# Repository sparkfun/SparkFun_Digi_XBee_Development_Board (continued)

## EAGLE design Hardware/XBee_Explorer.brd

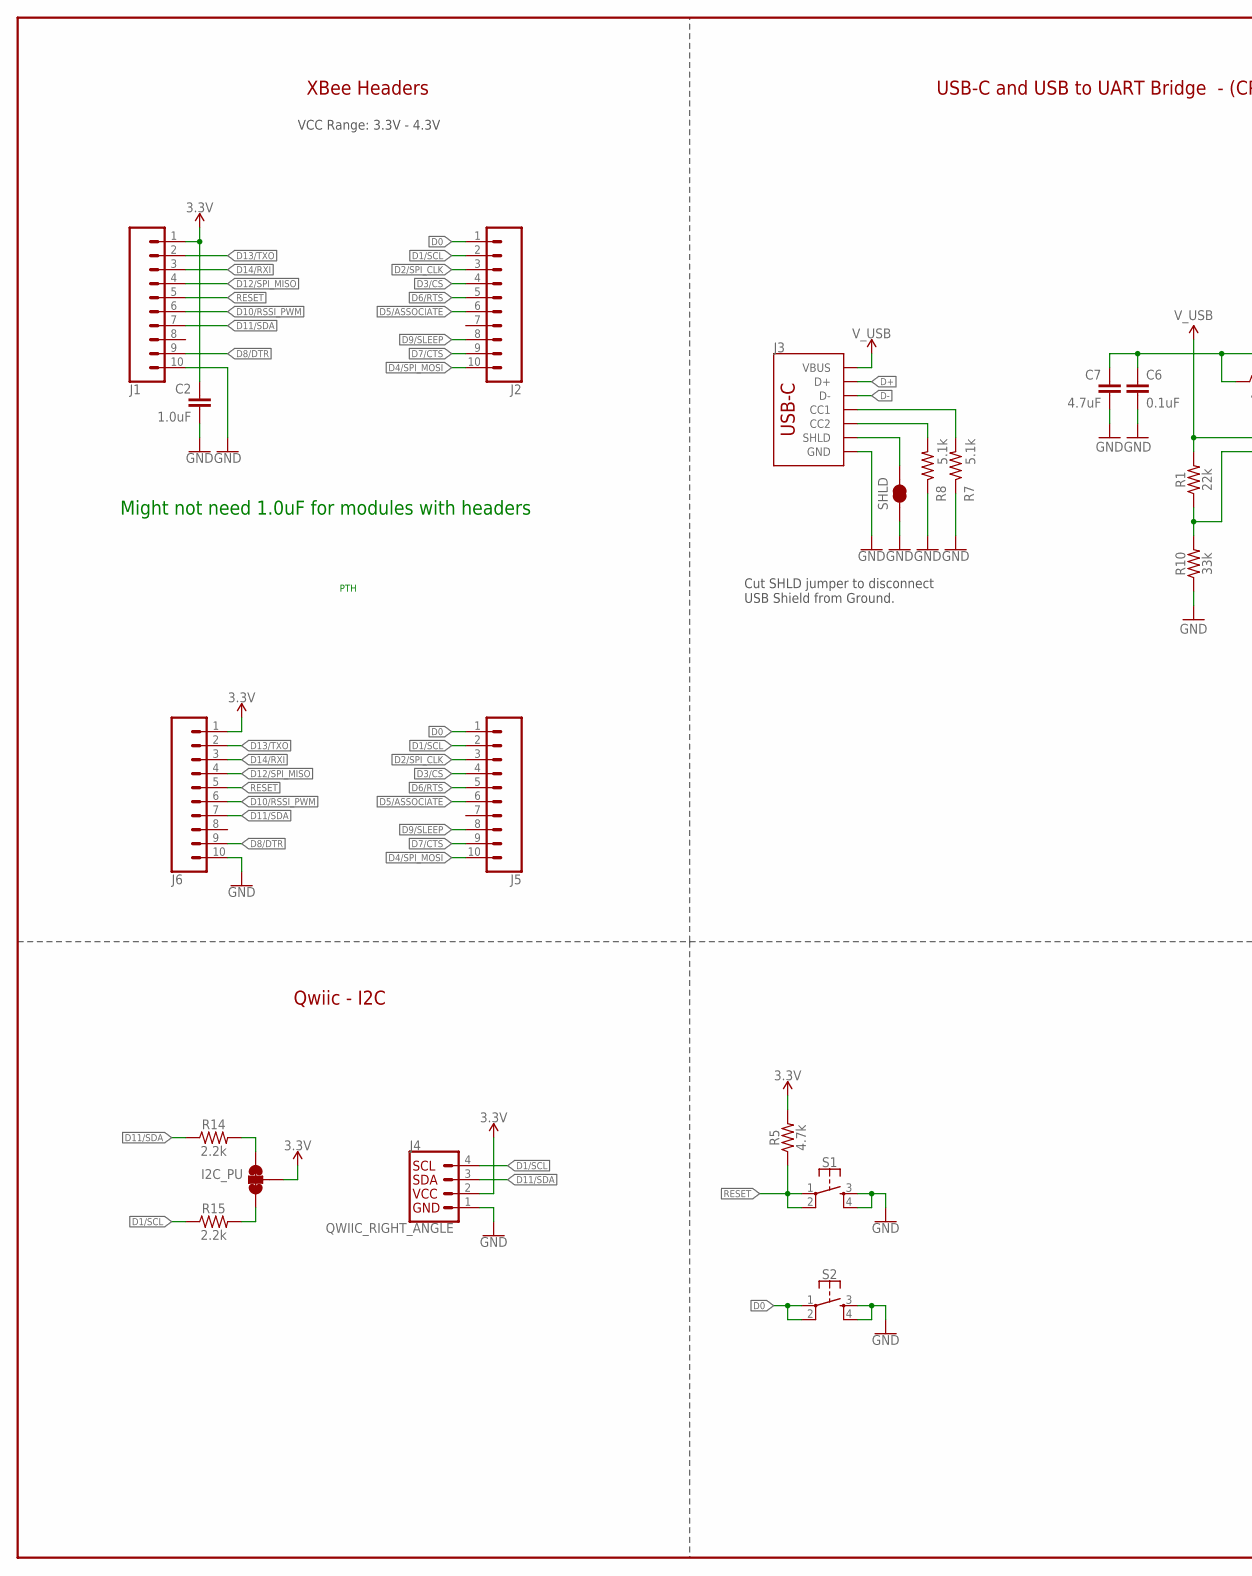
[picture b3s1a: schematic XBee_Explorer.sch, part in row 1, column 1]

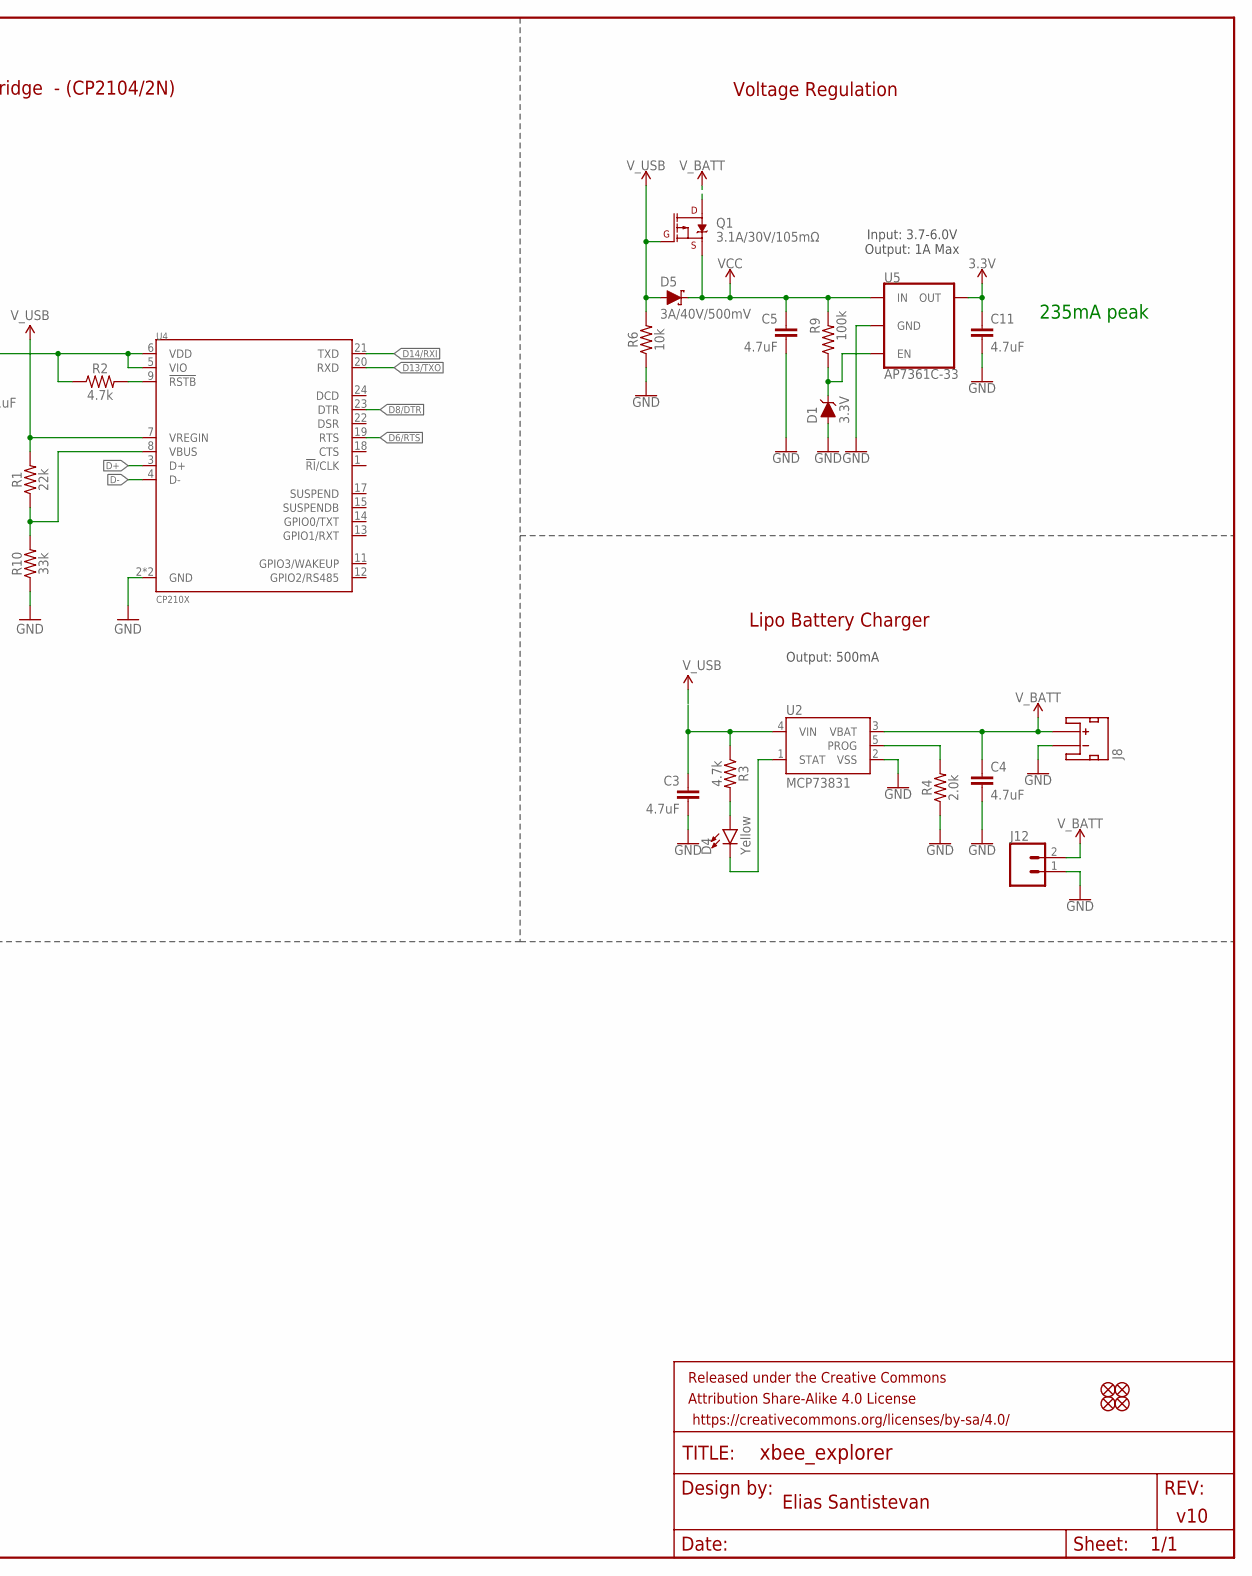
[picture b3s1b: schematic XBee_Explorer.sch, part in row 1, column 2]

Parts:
C2: 1.0uF; 0603
C3, C4, C5, C7, C11: 4.7uF; 0603
C6: 0.1uF; 0603
D1: 3.3V; SOD-323
D4: Yellow; LED-0603
D5: 3A/40V/500mV; SMA-DIODE
FD1, FD2, FD3, FD4: FIDUCIAL1X2; FIDUCIAL-1X2
FRAME1: FRAME-LEDGER; CREATIVE_COMMONS
I2C_PU: JUMPER-SMT_3_2-NC_TRACE_SILK; SMT-JUMPER_3_2-NC_TRACE_SILK
J1, J2, J5, J6: CONN_10NO_SILK_PTH_FEMALE; 1X10_NO_SILK
J3: USB_C_2-LAYER_PADS; USB-C-16P-2LAYER-PADS
J4: QWIIC_RIGHT_ANGLE; JST04_1MM_RA
J8: JST_2MM_MALE; JST-2-SMD
J12: CONN_021X02_NO_SILK; 1X02_NO_SILK
Q1: 3.1A/30V/105mΩ; SOT23-3
R1: 22k; 0603
R2, R3, R5: 4.7k; 0603
R4: 2.0k; 0603
R6: 10k; 0603
R7, R8: 5.1k; 0603
R9: 100k; 0603
R10: 33k; 0603
R14, R15: 2.2k; 0603
S1, S2: MOMENTARY-SWITCH-SPST-2-SMD-5.2MM-TALL; TACTILE_SWITCH_SMD_5.2MM
SHLD: JUMPER-SMT_2_NC_TRACE_SILK; SMT-JUMPER_2_NC_TRACE_SILK
U2: MCP73831; SOT23-5
U4: CP210X; QFN24
U5: AP7361C-33; UDFN-8

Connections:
3.3V: C2.1, C11.1, I2C_PU.2, J1.1, J4.2, J6.1, R5.2, U5.1 (OUT)
3.3V_EN_VE: D1.C, R9.1, U5.5 (EN)
!RESET!: J1.5, J6.5, R5.1, S1.1, S1.2
D0: J2.1, J5.1, S2.1, S2.2
D1/SCL: J2.2, J4.4, J5.2, R15.1
D2/SPI_CLK: J2.3, J5.3
D3/!CS!: J2.4, J5.4
D4/SPI_MOSI: J2.10, J5.10
D5/ASSOCIATE: J2.6, J5.6
D6/!RTS!: J2.5, J5.5, U4.19 (RTS)
D7/!CTS!: J2.9, J5.9
D8/!DTR!: J1.9, J6.9, U4.23 (DTR)
D9/!SLEEP!: J2.8, J5.8
D10/RSSI_PWM: J1.6, J6.6
D11/SDA: J1.7, J4.3, J6.7, R14.1
D12/SPI_MISO: J1.4, J6.4
D13/TXO: J1.2, J6.2, U4.20 (RXD)
D14/RXI: J1.3, J6.3, U4.21 (TXD)
D+: J3.A6 (D+), J3.B6 (D+), U4.3 (D+)
D-: J3.A7 (D-), J3.B7 (D-), U4.4 (D-)
GND: C2.2, C3.2, C4.2, C5.2, C6.2, C7.2, C11.2, D1.A, J1.10, J3.GND, J3.GND2 (GND), J4.1, J6.10, J8.1 (-), J12.1, R4.1, R6.1, R7.1, R8.1, R10.1, S1.3, S1.4, S2.3, S2.4, SHLD.1, U2.2 (VSS), U4.2 (GND), U4.PAD (GND), U5.4 (GND), U5.EP (GND)
unnamed: R4.2, U2.5 (PROG)
unnamed: R1.1, R10.2, U4.8 (VBUS)
unnamed: C6.1, C7.1, R2.1, U4.5 (VIO), U4.6 (VDD)
unnamed: J3.B5 (CC2), R8.2
unnamed: J3.A5 (CC1), R7.2
unnamed: R2.2, U4.9 (!RSTB)
unnamed: D4.C, U2.1 (STAT)
unnamed: D4.A, R3.2
unnamed: C3.1, R3.1, U2.4 (VIN)
unnamed: I2C_PU.3, R14.2
unnamed: I2C_PU.1, R15.2
SHLD: J3.SHLD1 (SHLD), J3.SHLD2 (SHLD), J3.SHLD3 (SHLD), J3.SHLD4 (SHLD), SHLD.2
VCC: C5.1, D5.C, Q1.2 (S), R9.2, U5.8 (IN)
V_BATT: C4.1, J8.2 (+), J12.2, Q1.3 (D), U2.3 (VBAT)
V_USB: D5.A, J3.VBUS1 (VBUS), J3.VBUS2 (VBUS), Q1.1 (G), R1.2, R6.2, U4.7 (VREGIN)

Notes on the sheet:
VCC Range: 3.3V - 4.3V
USB-C and USB to UART Bridge - (CP2104/2N)
Voltage Regulation
Input: 3.7-6.0V Output: 1A Max
Lipo Battery Charger
Output: 500mA
Cut SHLD jumper to disconnect USB Shield from Ground.
XBee Headers
Qwiic - I2C
235mA peak
v10
Elias Santistevan
Might not need 1.0uF for modules with headers
PTH

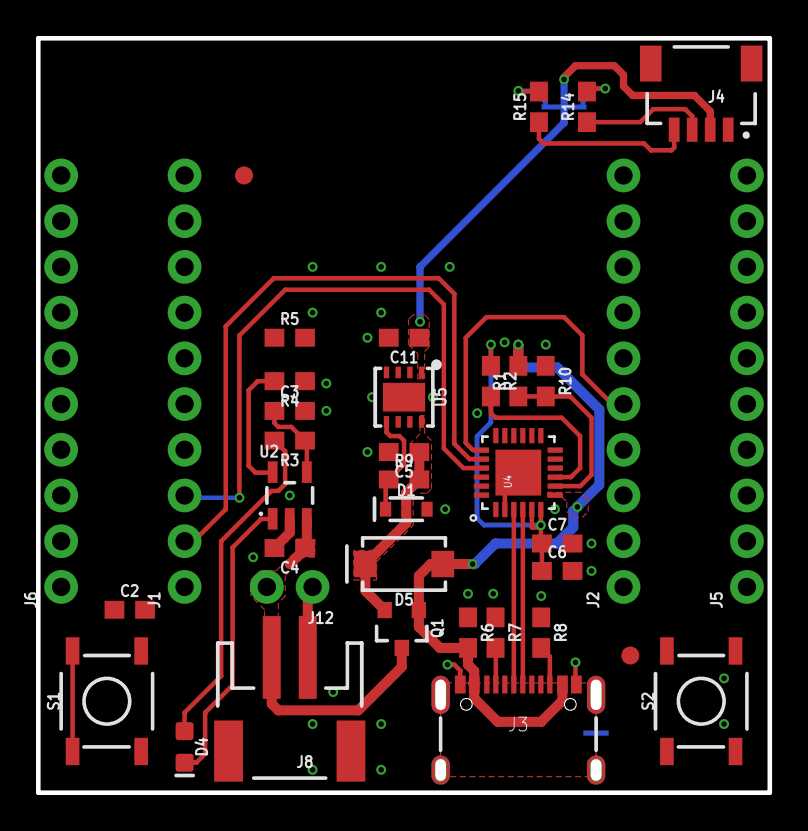
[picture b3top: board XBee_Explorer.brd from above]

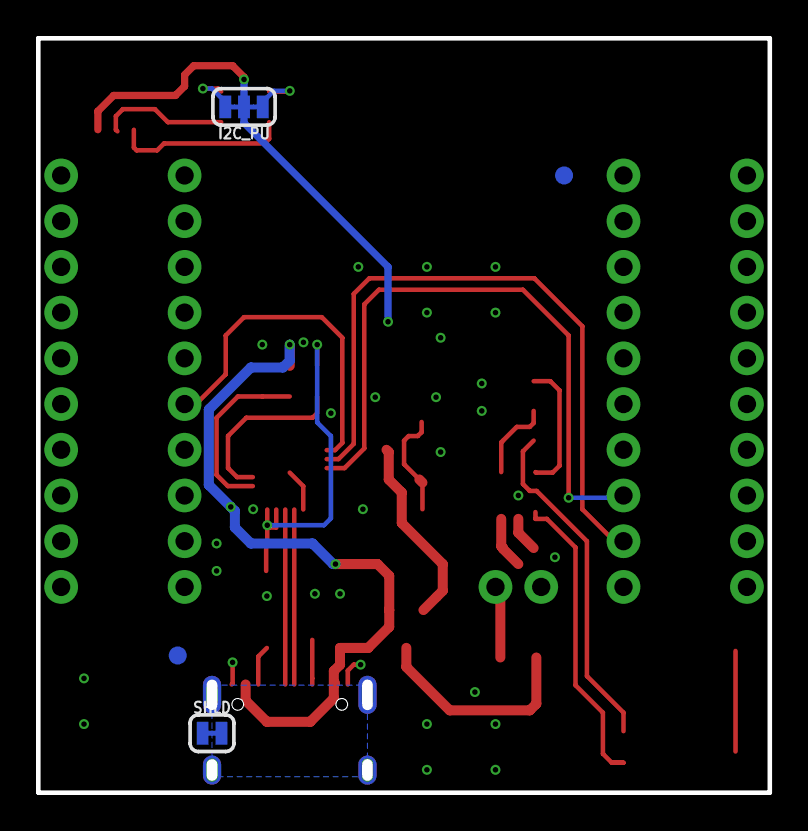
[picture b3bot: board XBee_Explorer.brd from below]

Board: 2 copper layers, 40.6 x 41.9 mm, 43 parts (4 on the bottom side), 36 nets.

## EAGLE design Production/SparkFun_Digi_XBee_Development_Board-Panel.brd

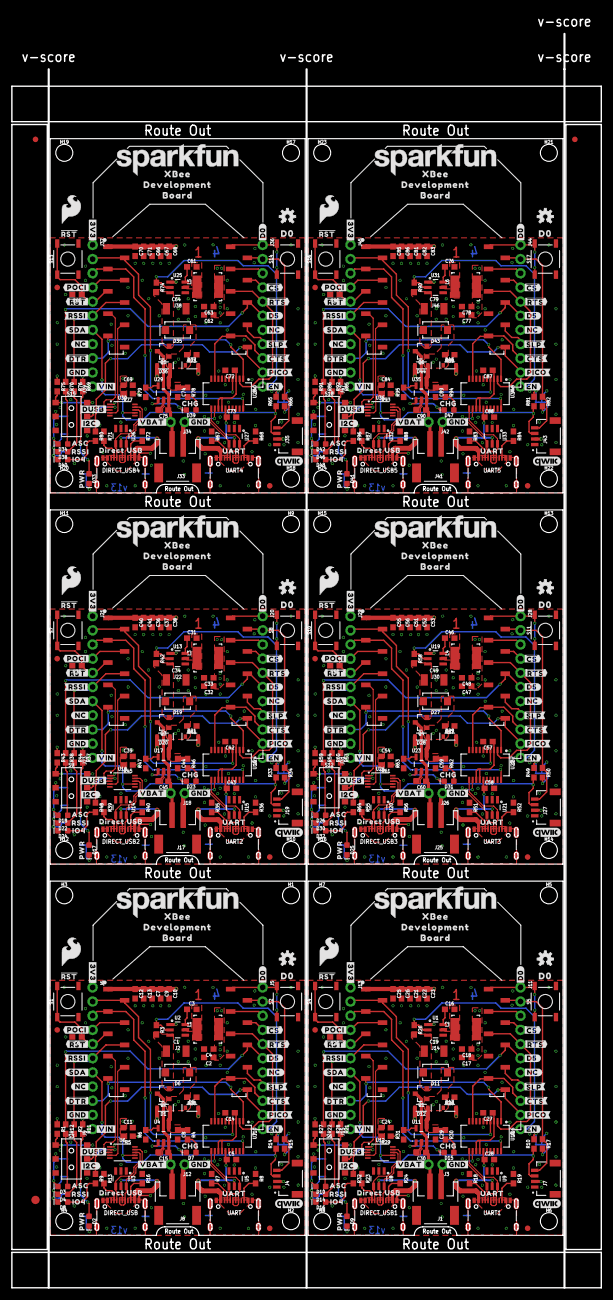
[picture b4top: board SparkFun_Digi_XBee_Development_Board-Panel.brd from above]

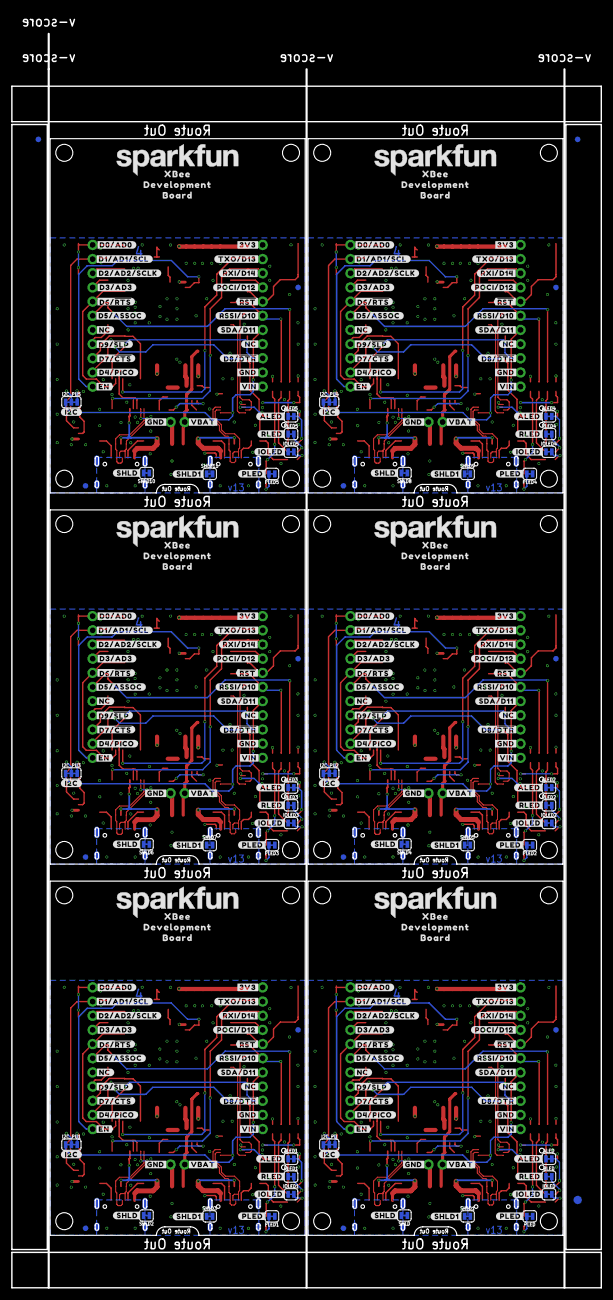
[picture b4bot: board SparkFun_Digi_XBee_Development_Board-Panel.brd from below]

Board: 4 copper layers, 105.7 x 224.8 mm, 894 parts (267 on the bottom side), 330 nets.

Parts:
ALED, ALED1, ALED2, ALED3, ALED4, ALED5: JUMPER-SMT_2_NC_TRACE_SILK; SMT-JUMPER_2_NC_TRACE_SILK
C1, C19, C34, C49, C64, C79: 10uF; 1210
C2, C4, C17, C18, C32, C33, C47, C48, C62, C63, C77, C78: 22uF; 0603
C3, C5, C9, C11, C14, C16, C22, C24, C27, C28, C31, C37, C39, C42, C43, C46, C52, C54, C57, C58, C61, C67, C69, C72, C73, C76, C82, C84, C87, C88: 0.1uF; 0603
C6, C7, C20, C21, C35, C36, C50, C51, C65, C66, C80, C81: 10nF; 0603
C8, C15, C29, C30, C44, C45, C59, C60, C74, C75, C89, C90: 4.7uF; 0603
C10, C23, C38, C53, C68, C83: 10uF; 0603
C12, C25, C40, C55, C70, C85: 10pF; 0603
C13, C26, C41, C56, C71, C86: 47pF; 0603
D1, D5, D12, D13, D20, D21, D28, D29, D36, D37, D44, D45: 3A/10V/280mV; SOD-323
D2, D9, D17, D25, D33, D41: RED; LED-0603
D3, D10, D18, D26, D34, D42: BLUE; LED-0603
D4, D7, D14, D15, D22, D23, D30, D31, D38, D39, D46, D47: Yellow; LED-0603
D6, D11, D19, D27, D35, D43: 3A/40V/500mV; SMA-DIODE
D8, D16, D24, D32, D40, D48: GREEN; LED-0603
DIRECT_USB, DIRECT_USB1, DIRECT_USB2, DIRECT_USB3, DIRECT_USB4, DIRECT_USB5: USB Female Type C Connector; USB-C-16P-4LAYER-ISOLATED
E$1, E$2, E$3, E$4: FIDUCIAL-1X2
E$5, E$6: FIDUCIAL-1.5X3
FD1, FD2, FD3, FD4, FD5, FD6, FD7, FD8, FD9, FD10, FD11, FD12, FD13, FD14, FD15, FD16, FD17, FD18, FD19, FD20, FD21, FD22, FD23, FD24: FIDUCIAL1X2; FIDUCIAL-1X2
H1, H2, H3, H4, H5, H6, H7, H8, H9, H10, H11, H12, H13, H14, H15, H16, H17, H18, H19, H20, H21, H22, H23, H24: STAND-OFFTIGHT; STAND-OFF-TIGHT
I2C_PU, I2C_PU1, I2C_PU2, I2C_PU3, I2C_PU4, I2C_PU5: JUMPER-SMT_3_2-NC_TRACE_SILK; SMT-JUMPER_3_2-NC_TRACE_SILK
IOLED, IOLED1, IOLED2, IOLED3, IOLED4, IOLED5: JUMPER-SMT_2_NC_TRACE_SILK; SMT-JUMPER_2_NC_TRACE_SILK
J1, J8, J17, J25, J33, J41: JST-2-SMD
J2, J14, J22, J30, J38, J46: XBEE3-SMD
J3, J12, J18, J26, J34, J42: 1X02_NO_SILK
J4, J7, J19, J27, J35, J43: QWIIC_RIGHT_ANGLE; JST04_1MM_RA
J5, J6, J11, J13, J20, J21, J28, J29, J36, J37, J44, J45: 1X10_NO_SILK
J9, J10, J15, J16, J23, J24, J31, J32, J39, J40, J47, J48: 1X01_NO_SILK_STAND
L1, L2, L3, L4, L5, L6: 3.9UH; INDUCTOR_3.9UH
LOGO1, LOGO6, LOGO9, LOGO12, LOGO15, LOGO18: SFE_LOGO_NAME.2_INCH; SFE_LOGO_NAME_.2
LOGO2, LOGO4, LOGO7, LOGO10, LOGO13, LOGO16: OSHW-LOGOS; OSHW-LOGO-S
LOGO3, LOGO5, LOGO8, LOGO11, LOGO14, LOGO17: QWIIC_LOGO_5MM; QWIIC_5MM
PLED, PLED1, PLED2, PLED3, PLED4, PLED5: JUMPER-SMT_2_NC_TRACE_SILK; SMT-JUMPER_2_NC_TRACE_SILK
Q1, Q2, Q3, Q4, Q5, Q6: 3.1A/30V/105mΩ; SOT23-3
R1, R27, R43, R59, R75, R91: 100k; 0603
R2, R10, R12, R14, R15, R17, R22, R28, R33, R34, R38, R44, R49, R50, R54, R60, R65, R66, R70, R76, R81, R82, R86, R92: 2.2k; 0603
R3, R20, R25, R26, R41, R42, R57, R58, R73, R74, R89, R90: 10k; 0603
R4, R11, R21, R30, R37, R46, R53, R62, R69, R78, R85, R94: 4.7k; 0603
R5, R29, R45, R61, R77, R93: 0; 0603
R6, R31, R47, R63, R79, R95: 2.0k; 0603
R7, R8, R13, R16, R18, R19, R23, R24, R35, R36, R39, R40, R51, R52, R55, R56, R67, R68, R71, R72, R83, R84, R87, R88: 5.1k; 0603
R9, R32, R48, R64, R80, R96: 330; 0603
RLED, RLED1, RLED2, RLED3, RLED4, RLED5: JUMPER-SMT_2_NC_TRACE_SILK; SMT-JUMPER_2_NC_TRACE_SILK
S1, S2, S4, S5, S7, S8, S10, S11, S13, S14, S16, S17: TACTILE_SWITCH_SMD_5.2MM
S3, S6, S9, S12, S15, S18: SWITCH_DPDT_SMD_AYZ0202
SHLD, SHLD1, SHLD2, SHLD3, SHLD4, SHLD5, SHLD6, SHLD7, SHLD8, SHLD9, SHLD10, SHLD11: JUMPER-SMT_2_NC_TRACE_SILK; SMT-JUMPER_2_NC_TRACE_SILK
U1, U2, U13, U19, U25, U31: AP63203; SOT23-6
U3, U5, U8, U9, U14, U15, U20, U21, U26, U27, U32, U33: ESD Diode; SOT-23-6
U4, U11, U17, U23, U29, U35: MCP73831; SOT23-5
U6, U12, U18, U24, U30, U36: FSUSB42MUX; MSOP10
U7, U10, U16, U22, U28, U34: FT231XS; SSOP20_L
U$1, U$135, U$205, U$275, U$345, U$415: #D2#AD2#SCLK#19
U$2, U$17, U$91, U$104, U$161, U$174, U$231, U$244, U$301, U$314, U$371, U$384: ##RST##15
U$3, U$69, U$141, U$211, U$281, U$351: ##CS##19
U$4, U$72, U$142, U$212, U$282, U$352: ##CTS##25
U$5, U$117, U$187, U$257, U$327, U$397: ##DTR##27
U$6, U$132, U$202, U$272, U$342, U$412: #D1#AD1#SCL#8
U$7, U$73, U$143, U$213, U$283, U$353: ##RTS##24
U$8, U$21, U$118, U$119, U$188, U$189, U$258, U$259, U$328, U$329, U$398, U$399: #EN#17
U$9, U$44, U$74, U$85, U$144, U$155, U$214, U$225, U$284, U$295, U$354, U$365: #3V3#1
U$10, U$75, U$145, U$215, U$285, U$355: #D0#18
U$11, U$37, U$92, U$107, U$162, U$177, U$232, U$247, U$302, U$317, U$372, U$387: #VBAT#5
U$12, U$96, U$166, U$236, U$306, U$376: #D3#AD3#22
U$13, U$97, U$167, U$237, U$307, U$377: #D4#PICO#24
U$14, U$115, U$185, U$255, U$325, U$395: #POCI#D12#24
U$15, U$102, U$172, U$242, U$312, U$382: #TXO#D13#13
U$16, U$103, U$173, U$243, U$313, U$383: #RXI#D14#15
U$18, U$105, U$175, U$245, U$315, U$385: #RSSI#D10#17
U$19, U$136, U$206, U$276, U$346, U$416: CHG47
U$20, U$25, U$38, U$45, U$76, U$81, U$86, U$108, U$146, U$151, U$156, U$178, U$216, U$221, U$226, U$248, U$286, U$291, U$296, U$318, U$356, U$361, U$366, U$388: #GND#0
U$22, U$106, U$176, U$246, U$316, U$386: #SDA#D11#8
U$23, U$50, U$130, U$131, U$200, U$201, U$270, U$271, U$340, U$341, U$410, U$411: XBEE339
U$24, U$67, U$120, U$123, U$190, U$193, U$260, U$263, U$330, U$333, U$400, U$403: #NC#1
U$26, U$77, U$147, U$217, U$287, U$357: #I2C#33
U$27, U$93, U$163, U$233, U$303, U$373: #ALED#21
U$28, U$78, U$148, U$218, U$288, U$358: #PICO#23
U$29, U$116, U$186, U$256, U$326, U$396: #POCI#23
U$30, U$110, U$180, U$250, U$320, U$390: #RST#30
U$31, U$79, U$149, U$219, U$289, U$359: #RSSI#16
U$32, U$129, U$199, U$269, U$339, U$409: #DUSB#31
U$33, U$137, U$207, U$277, U$347, U$417: IO46
U$34, U$80, U$150, U$220, U$290, U$360: #SDA#7
U$35, U$138, U$208, U$278, U$348, U$418: #SHLD#740
U$36, U$139, U$209, U$279, U$349, U$419: #SHLD1#741
U$39, U$82, U$152, U$222, U$292, U$362: #D5#3
U$40, U$90, U$160, U$230, U$300, U$370: D03
U$41, U$46, U$83, U$87, U$153, U$157, U$223, U$227, U$293, U$297, U$363, U$367: #VIN#4
U$42, U$84, U$154, U$224, U$294, U$364: PWR26
U$43, U$134, U$204, U$274, U$344, U$414: ASC32
U$47, U$88, U$158, U$228, U$298, U$368: ##SLP##27
U$48, U$66, U$121, U$122, U$191, U$192, U$261, U$262, U$331, U$332, U$401, U$402: #NC#3
U$49, U$89, U$159, U$229, U$299, U$369: #I2C#31
U$51, U$70, U$125, U$127, U$195, U$197, U$265, U$267, U$335, U$337, U$405, U$407: DEVELOPMENT1345
U$52, U$71, U$126, U$128, U$196, U$198, U$266, U$268, U$336, U$338, U$406, U$408: BOARD1346
U$53, U$133, U$203, U$273, U$343, U$413: #D8##DTR##27
U$54, U$94, U$164, U$234, U$304, U$374: #PLED#20
U$55, U$95, U$165, U$235, U$305, U$375: #D0#AD0#18
U$56, U$98, U$168, U$238, U$308, U$378: #D5#ASSOC#24
U$57, U$99, U$169, U$239, U$309, U$379: #D6##RTS##24
U$58, U$100, U$170, U$240, U$310, U$380: #D7##CTS##25
U$59, U$140, U$210, U$280, U$350, U$420: #IOLED#23
U$60, U$101, U$171, U$241, U$311, U$381: #D9##SLP##27
U$61, U$112, U$182, U$252, U$322, U$392: SFE_LOGO_FLAME_.2
U$62, U$113, U$183, U$253, U$323, U$393: RSSI31
U$63, U$111, U$181, U$251, U$321, U$391: SFE_LOGO_NAME_.2
U$64, U$114, U$184, U$254, U$324, U$394: #RLED#22
U$65, U$109, U$179, U$249, U$319, U$389: UART32
U$68, U$124, U$194, U$264, U$334, U$404: DIRECT_USB33
UART, UART1, UART2, UART3, UART4, UART5: USB Female Type C Connector; USB-C-16P-4LAYER-ISOLATED

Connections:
3.3V: C2.1, C4.1, C7.1, C9.1, C10.1, C11.1, C12.1, C13.1, I2C_PU.2, J2.1, J4.2, J6.1, L1.P$2, R1.1, R5.2, R11.1, U2.1
3.3V1: C17.1, C18.1, C21.1, C22.1, C23.1, C24.1, C25.1, C26.1, I2C_PU1.2, J7.2, J13.1, J14.1, L2.P$2, R21.1, R27.1, R29.2, U1.1
3.3V2: C32.1, C33.1, C36.1, C37.1, C38.1, C39.1, C40.1, C41.1, I2C_PU2.2, J19.2, J21.1, J22.1, L3.P$2, R37.1, R43.1, R45.2, U13.1
3.3V3: C47.1, C48.1, C51.1, C52.1, C53.1, C54.1, C55.1, C56.1, I2C_PU3.2, J27.2, J29.1, J30.1, L4.P$2, R53.1, R59.1, R61.2, U19.1
3.3V4: C62.1, C63.1, C66.1, C67.1, C68.1, C69.1, C70.1, C71.1, I2C_PU4.2, J35.2, J37.1, J38.1, L5.P$2, R69.1, R75.1, R77.2, U25.1
3.3V5: C77.1, C78.1, C81.1, C82.1, C83.1, C84.1, C85.1, C86.1, I2C_PU5.2, J43.2, J45.1, J46.1, L6.P$2, R85.1, R91.1, R93.2, U31.1
!RESET!: C6.1, J2.5, J6.5, S1.1, S1.2
!RESET!1: C20.1, J13.5, J14.5, S4.1, S4.2
!RESET!2: C35.1, J21.5, J22.5, S7.1, S7.2
!RESET!3: C50.1, J29.5, J30.5, S10.1, S10.2
!RESET!4: C65.1, J37.5, J38.5, S13.1, S13.2
!RESET!5: C80.1, J45.5, J46.5, S16.1, S16.2
ALED: ALED.2, D3.C
ALED1: ALED1.2, D10.C
ALED2: ALED2.2, D18.C
ALED3: ALED3.2, D26.C
ALED4: ALED4.2, D34.C
ALED5: ALED5.2, D42.C
D0: J2.20, J5.1, S2.1, S2.2
D1: J11.1, J14.20, S5.1, S5.2
D1/SCL: J2.19, J4.4, J5.2, R15.1
D1/SCL1: J7.4, J11.2, J14.19, R17.1
D1/SCL2: J19.4, J20.2, J22.19, R34.1
D1/SCL3: J27.4, J28.2, J30.19, R50.1
D1/SCL4: J35.4, J36.2, J38.19, R66.1
D1/SCL5: J43.4, J44.2, J46.19, R82.1
D2: J20.1, J22.20, S8.1, S8.2
D2/SPI_CLK: J2.18, J5.3
D2/SPI_CLK1: J11.3, J14.18
D2/SPI_CLK2: J20.3, J22.18
D2/SPI_CLK3: J28.3, J30.18
D2/SPI_CLK4: J36.3, J38.18
D2/SPI_CLK5: J44.3, J46.18
D3: J28.1, J30.20, S11.1, S11.2
D3/SPI_!CS!: J2.17, J5.4
D3/SPI_!CS!1: J11.4, J14.17
D3/SPI_!CS!2: J20.4, J22.17
D3/SPI_!CS!3: J28.4, J30.17
D3/SPI_!CS!4: J36.4, J38.17
D3/SPI_!CS!5: J44.4, J46.17
D4: J36.1, J38.20, S14.1, S14.2
D4/SPI_PICO: J2.11, J5.10, R9.1
D4/SPI_PICO1: J11.10, J14.11, R32.1
D4/SPI_PICO2: J20.10, J22.11, R48.1
D4/SPI_PICO3: J28.10, J30.11, R64.1
D4/SPI_PICO4: J36.10, J38.11, R80.1
D4/SPI_PICO5: J44.10, J46.11, R96.1
D5: J44.1, J46.20, S17.1, S17.2
D5/ASSOCIATE: J2.15, J5.6, R12.1
D5/ASSOCIATE1: J11.6, J14.15, R22.1
D5/ASSOCIATE2: J20.6, J22.15, R38.1
D5/ASSOCIATE3: J28.6, J30.15, R54.1
D5/ASSOCIATE4: J36.6, J38.15, R70.1
D5/ASSOCIATE5: J44.6, J46.15, R86.1
D6/!RTS!: J2.16, J5.5, U7.2
D6/!RTS!1: J11.5, J14.16, U10.2
D6/!RTS!2: J20.5, J22.16, U16.2
D6/!RTS!3: J28.5, J30.16, U22.2
D6/!RTS!4: J36.5, J38.16, U28.2
D6/!RTS!5: J44.5, J46.16, U34.2
D7/!CTS!: J2.12, J5.9, U7.9
D7/!CTS!1: J11.9, J14.12, U10.9
D7/!CTS!2: J20.9, J22.12, U16.9
D7/!CTS!3: J28.9, J30.12, U22.9
D7/!CTS!4: J36.9, J38.12, U28.9
D7/!CTS!5: J44.9, J46.12, U34.9
D8/!DTR!: J2.9, J6.9, U7.1
D8/!DTR!1: J13.9, J14.9, U10.1
D8/!DTR!2: J21.9, J22.9, U16.1
D8/!DTR!3: J29.9, J30.9, U22.1
D8/!DTR!4: J37.9, J38.9, U28.1
D8/!DTR!5: J45.9, J46.9, U34.1
D9/!SLEEP!: J2.13, J5.8
D9/!SLEEP!1: J11.8, J14.13
D9/!SLEEP!2: J20.8, J22.13
D9/!SLEEP!3: J28.8, J30.13
D9/!SLEEP!4: J36.8, J38.13
D9/!SLEEP!5: J44.8, J46.13
D10/RSSI_PWM: J2.6, J6.6, R2.1
D10/RSSI_PWM1: J13.6, J14.6, R28.1
D10/RSSI_PWM2: J21.6, J22.6, R44.1
D10/RSSI_PWM3: J29.6, J30.6, R60.1
D10/RSSI_PWM4: J37.6, J38.6, R76.1
D10/RSSI_PWM5: J45.6, J46.6, R92.1
D11/SDA: J4.3, J6.7, R14.1, U6.7
D11/SDA1: J7.3, J13.7, R10.1, U12.7
D11/SDA2: J19.3, J21.7, R33.1, U18.7
D11/SDA3: J27.3, J29.7, R49.1, U24.7
D11/SDA4: J35.3, J37.7, R65.1, U30.7
D11/SDA5: J43.3, J45.7, R81.1, U36.7
D12/SPI_POCI: J2.4, J6.4
D12/SPI_POCI1: J13.4, J14.4
D12/SPI_POCI2: J21.4, J22.4
D12/SPI_POCI3: J29.4, J30.4
D12/SPI_POCI4: J37.4, J38.4
D12/SPI_POCI5: J45.4, J46.4
D13/TXO: J2.2, J6.2, U7.4
D13/TXO1: J13.2, J14.2, U10.4
D13/TXO2: J21.2, J22.2, U16.4
D13/TXO3: J29.2, J30.2, U22.4
D13/TXO4: J37.2, J38.2, U28.4
D13/TXO5: J45.2, J46.2, U34.4
D14/RXI: J2.3, J6.3, U7.20
D14/RXI1: J13.3, J14.3, U10.20
D14/RXI2: J21.3, J22.3, U16.20
D14/RXI3: J29.3, J30.3, U22.20
D14/RXI4: J37.3, J38.3, U28.20
D14/RXI5: J45.3, J46.3, U34.20
D+: U5.6, U7.11, UART.A6, UART.B6
D+1: U9.6, U10.11, UART1.A6, UART1.B6
D+2: U15.6, U16.11, UART2.A6, UART2.B6
D+3: U21.6, U22.11, UART3.A6, UART3.B6
D+4: U27.6, U28.11, UART4.A6, UART4.B6
D+5: U33.6, U34.11, UART5.A6, UART5.B6
D-: U5.4, U7.12, UART.A7, UART.B7
D-1: U9.4, U10.12, UART1.A7, UART1.B7
D-2: U15.4, U16.12, UART2.A7, UART2.B7
D-3: U21.4, U22.12, UART3.A7, UART3.B7
D-4: U27.4, U28.12, UART4.A7, UART4.B7
D-5: U33.4, U34.12, UART5.A7, UART5.B7
DIRECT_D+: DIRECT_USB.A6, DIRECT_USB.B6, U3.6, U6.9
DIRECT_D+1: DIRECT_USB1.A6, DIRECT_USB1.B6, U8.6, U12.9
DIRECT_D+2: DIRECT_USB2.A6, DIRECT_USB2.B6, U14.6, U18.9
DIRECT_D+3: DIRECT_USB3.A6, DIRECT_USB3.B6, U20.6, U24.9
DIRECT_D+4: DIRECT_USB4.A6, DIRECT_USB4.B6, U26.6, U30.9
DIRECT_D+5: DIRECT_USB5.A6, DIRECT_USB5.B6, U32.6, U36.9
DIRECT_D-: DIRECT_USB.A7, DIRECT_USB.B7, U3.4, U6.8
DIRECT_D-1: DIRECT_USB1.A7, DIRECT_USB1.B7, U8.4, U12.8
DIRECT_D-2: DIRECT_USB2.A7, DIRECT_USB2.B7, U14.4, U18.8
DIRECT_D-3: DIRECT_USB3.A7, DIRECT_USB3.B7, U20.4, U24.8
DIRECT_D-4: DIRECT_USB4.A7, DIRECT_USB4.B7, U26.4, U30.8
DIRECT_D-5: DIRECT_USB5.A7, DIRECT_USB5.B7, U32.4, U36.8
DIRECT_SELECT: S3.2, S3.5, U6.2
DIRECT_SELECT1: S6.2, S6.5, U12.2
DIRECT_SELECT2: S9.2, S9.5, U18.2
DIRECT_SELECT3: S12.2, S12.5, U24.2
DIRECT_SELECT4: S15.2, S15.5, U30.2
DIRECT_SELECT5: S18.2, S18.5, U36.2
EN: J10.1, R3.1, U2.2
EN1: J16.1, R26.1, U1.2
EN2: J24.1, R42.1, U13.2
EN3: J32.1, R58.1, U19.2
EN4: J40.1, R74.1, U25.2
EN5: J48.1, R90.1, U31.2
FIRMWARE: R1.2, S3.1, S3.4
FIRMWARE1: R27.2, S6.1, S6.4
FIRMWARE2: R43.2, S9.1, S9.4
FIRMWARE3: R59.2, S12.1, S12.4
FIRMWARE4: R75.2, S15.1, S15.4
FIRMWARE5: R91.2, S18.1, S18.4
GND: ALED.1, C1.2, C2.2, C4.2, C5.2, C6.2, C7.2, C8.2, C9.2, C10.2, C11.2, C12.2, C13.2, C14.2, C15.2, DIRECT_USB.GND, DIRECT_USB.GND2, IOLED.1, J2.10, J4.1, J6.10, J8.1, J12.1, PLED.1, R6.1, R7.1, R8.1, R13.1, R16.1, R20.1, RLED.1, S1.3, S1.4, S2.3, S2.4, S3.3, S3.6, SHLD.1, SHLD1.1, U2.4, U3.2, U4.2, U5.2, U6.5, U6.10, U7.6, U7.16, UART.GND, UART.GND2
GND1: ALED1.1, C17.2, C18.2, C19.2, C20.2, C21.2, C22.2, C23.2, C24.2, C25.2, C26.2, C27.2, C28.2, C29.2, C30.2, DIRECT_USB1.GND, DIRECT_USB1.GND2, IOLED1.1, J1.1, J3.1, J7.1, J13.10, J14.10, PLED1.1, R18.1, R19.1, R23.1, R24.1, R25.1, R31.1, RLED1.1, S4.3, S4.4, S5.3, S5.4, S6.3, S6.6, SHLD2.1, SHLD3.1, U1.4, U8.2, U9.2, U10.6, U10.16, U11.2, U12.5, U12.10, UART1.GND, UART1.GND2
GND2: ALED2.1, C32.2, C33.2, C34.2, C35.2, C36.2, C37.2, C38.2, C39.2, C40.2, C41.2, C42.2, C43.2, C44.2, C45.2, DIRECT_USB2.GND, DIRECT_USB2.GND2, IOLED2.1, J17.1, J18.1, J19.1, J21.10, J22.10, PLED2.1, R35.1, R36.1, R39.1, R40.1, R41.1, R47.1, RLED2.1, S7.3, S7.4, S8.3, S8.4, S9.3, S9.6, SHLD4.1, SHLD5.1, U13.4, U14.2, U15.2, U16.6, U16.16, U17.2, U18.5, U18.10, UART2.GND, UART2.GND2
GND3: ALED3.1, C47.2, C48.2, C49.2, C50.2, C51.2, C52.2, C53.2, C54.2, C55.2, C56.2, C57.2, C58.2, C59.2, C60.2, DIRECT_USB3.GND, DIRECT_USB3.GND2, IOLED3.1, J25.1, J26.1, J27.1, J29.10, J30.10, PLED3.1, R51.1, R52.1, R55.1, R56.1, R57.1, R63.1, RLED3.1, S10.3, S10.4, S11.3, S11.4, S12.3, S12.6, SHLD6.1, SHLD7.1, U19.4, U20.2, U21.2, U22.6, U22.16, U23.2, U24.5, U24.10, UART3.GND, UART3.GND2
GND4: ALED4.1, C62.2, C63.2, C64.2, C65.2, C66.2, C67.2, C68.2, C69.2, C70.2, C71.2, C72.2, C73.2, C74.2, C75.2, DIRECT_USB4.GND, DIRECT_USB4.GND2, IOLED4.1, J33.1, J34.1, J35.1, J37.10, J38.10, PLED4.1, R67.1, R68.1, R71.1, R72.1, R73.1, R79.1, RLED4.1, S13.3, S13.4, S14.3, S14.4, S15.3, S15.6, SHLD8.1, SHLD9.1, U25.4, U26.2, U27.2, U28.6, U28.16, U29.2, U30.5, U30.10, UART4.GND, UART4.GND2
GND5: ALED5.1, C77.2, C78.2, C79.2, C80.2, C81.2, C82.2, C83.2, C84.2, C85.2, C86.2, C87.2, C88.2, C89.2, C90.2, DIRECT_USB5.GND, DIRECT_USB5.GND2, IOLED5.1, J41.1, J42.1, J43.1, J45.10, J46.10, PLED5.1, R83.1, R84.1, R87.1, R88.1, R89.1, R95.1, RLED5.1, S16.3, S16.4, S17.3, S17.4, S18.3, S18.6, SHLD10.1, SHLD11.1, U31.4, U32.2, U33.2, U34.6, U34.16, U35.2, U36.5, U36.10, UART5.GND, UART5.GND2
IOLED: D8.C, IOLED.2
IOLED1: D16.C, IOLED1.2
IOLED2: D24.C, IOLED2.2
IOLED3: D32.C, IOLED3.2
IOLED4: D40.C, IOLED4.2
IOLED5: D48.C, IOLED5.2
unnamed: C3.1, U2.6
unnamed: D4.A, R2.2
unnamed: R5.1, U6.1
unnamed: R8.2, UART.B5
unnamed: R7.2, UART.A5
unnamed: R6.2, U4.5
unnamed: D2.A, R11.2
unnamed: C3.2, L1.P$1, U2.5
unnamed: D7.C, U4.1
unnamed: D7.A, R4.2
unnamed: I2C_PU.3, R14.2
unnamed: D3.A, R12.2
unnamed: I2C_PU.1, R15.2
unnamed: DIRECT_USB.B5, R16.2
unnamed: C1.1, D6.C, Q2.2, R3.2, U2.3
unnamed: DIRECT_USB.A5, R13.2
unnamed: D8.A, R9.2
unnamed: C14.1, U7.3, U7.13, U7.14
unnamed: I2C_PU1.3, R10.2
unnamed: I2C_PU1.1, R17.2
unnamed: R19.2, UART1.B5
unnamed: R18.2, UART1.A5
unnamed: D9.A, R21.2
unnamed: D10.A, R22.2
unnamed: DIRECT_USB1.B5, R24.2
unnamed: DIRECT_USB1.A5, R23.2
unnamed: C19.1, D11.C, Q1.2, R26.2, U1.3
unnamed: C16.1, U1.6
unnamed: C16.2, L2.P$1, U1.5
unnamed: D14.A, R28.2
unnamed: R29.1, U12.1
unnamed: R31.2, U11.5
unnamed: D15.C, U11.1
unnamed: D15.A, R30.2
unnamed: D16.A, R32.2
unnamed: C27.1, U10.3, U10.13, U10.14
unnamed: I2C_PU2.3, R33.2
unnamed: I2C_PU2.1, R34.2
unnamed: R36.2, UART2.B5
unnamed: R35.2, UART2.A5
unnamed: D17.A, R37.2
unnamed: D18.A, R38.2
unnamed: DIRECT_USB2.B5, R40.2
unnamed: DIRECT_USB2.A5, R39.2
unnamed: C34.1, D19.C, Q3.2, R42.2, U13.3
unnamed: C31.1, U13.6
unnamed: C31.2, L3.P$1, U13.5
unnamed: D22.A, R44.2
unnamed: R45.1, U18.1
unnamed: R47.2, U17.5
unnamed: D23.C, U17.1
unnamed: D23.A, R46.2
unnamed: D24.A, R48.2
unnamed: C42.1, U16.3, U16.13, U16.14
unnamed: I2C_PU3.3, R49.2
unnamed: I2C_PU3.1, R50.2
unnamed: R52.2, UART3.B5
unnamed: R51.2, UART3.A5
unnamed: D25.A, R53.2
unnamed: D26.A, R54.2
unnamed: DIRECT_USB3.B5, R56.2
unnamed: DIRECT_USB3.A5, R55.2
unnamed: C49.1, D27.C, Q4.2, R58.2, U19.3
unnamed: C46.1, U19.6
unnamed: C46.2, L4.P$1, U19.5
unnamed: D30.A, R60.2
unnamed: R61.1, U24.1
unnamed: R63.2, U23.5
unnamed: D31.C, U23.1
unnamed: D31.A, R62.2
unnamed: D32.A, R64.2
unnamed: C57.1, U22.3, U22.13, U22.14
unnamed: I2C_PU4.3, R65.2
unnamed: I2C_PU4.1, R66.2
unnamed: R68.2, UART4.B5
unnamed: R67.2, UART4.A5
unnamed: D33.A, R69.2
unnamed: D34.A, R70.2
unnamed: DIRECT_USB4.B5, R72.2
unnamed: DIRECT_USB4.A5, R71.2
unnamed: C64.1, D35.C, Q5.2, R74.2, U25.3
unnamed: C61.1, U25.6
unnamed: C61.2, L5.P$1, U25.5
unnamed: D38.A, R76.2
unnamed: R77.1, U30.1
unnamed: R79.2, U29.5
unnamed: D39.C, U29.1
unnamed: D39.A, R78.2
unnamed: D40.A, R80.2
unnamed: C72.1, U28.3, U28.13, U28.14
unnamed: I2C_PU5.3, R81.2
unnamed: I2C_PU5.1, R82.2
unnamed: R84.2, UART5.B5
unnamed: R83.2, UART5.A5
unnamed: D41.A, R85.2
unnamed: D42.A, R86.2
unnamed: DIRECT_USB5.B5, R88.2
unnamed: DIRECT_USB5.A5, R87.2
unnamed: C79.1, D43.C, Q6.2, R90.2, U31.3
unnamed: C76.1, U31.6
unnamed: C76.2, L6.P$1, U31.5
unnamed: D46.A, R92.2
unnamed: R93.1, U36.1
unnamed: R95.2, U35.5
unnamed: D47.C, U35.1
unnamed: D47.A, R94.2
unnamed: D48.A, R96.2
unnamed: C87.1, U34.3, U34.13, U34.14
PLED: D2.C, PLED.2
PLED1: D9.C, PLED1.2
PLED2: D17.C, PLED2.2
PLED3: D25.C, PLED3.2
PLED4: D33.C, PLED4.2
PLED5: D41.C, PLED5.2
RLED: D4.C, RLED.2
RLED1: D14.C, RLED1.2
RLED2: D22.C, RLED2.2
RLED3: D30.C, RLED3.2
RLED4: D38.C, RLED4.2
RLED5: D46.C, RLED5.2
SHLD: SHLD.2, UART.SHLD1, UART.SHLD2, UART.SHLD3, UART.SHLD4, UART.SHLD5, UART.SHLD6, UART.SHLD7, UART.SHLD8
SHLD1: DIRECT_USB.SHLD1, DIRECT_USB.SHLD2, DIRECT_USB.SHLD3, DIRECT_USB.SHLD4, DIRECT_USB.SHLD5, DIRECT_USB.SHLD6, DIRECT_USB.SHLD7, DIRECT_USB.SHLD8, SHLD1.2
SHLD2: SHLD2.2, UART1.SHLD1, UART1.SHLD2, UART1.SHLD3, UART1.SHLD4, UART1.SHLD5, UART1.SHLD6, UART1.SHLD7, UART1.SHLD8
SHLD3: DIRECT_USB1.SHLD1, DIRECT_USB1.SHLD2, DIRECT_USB1.SHLD3, DIRECT_USB1.SHLD4, DIRECT_USB1.SHLD5, DIRECT_USB1.SHLD6, DIRECT_USB1.SHLD7, DIRECT_USB1.SHLD8, SHLD3.2
SHLD4: SHLD4.2, UART2.SHLD1, UART2.SHLD2, UART2.SHLD3, UART2.SHLD4, UART2.SHLD5, UART2.SHLD6, UART2.SHLD7, UART2.SHLD8
SHLD5: DIRECT_USB2.SHLD1, DIRECT_USB2.SHLD2, DIRECT_USB2.SHLD3, DIRECT_USB2.SHLD4, DIRECT_USB2.SHLD5, DIRECT_USB2.SHLD6, DIRECT_USB2.SHLD7, DIRECT_USB2.SHLD8, SHLD5.2
SHLD6: SHLD6.2, UART3.SHLD1, UART3.SHLD2, UART3.SHLD3, UART3.SHLD4, UART3.SHLD5, UART3.SHLD6, UART3.SHLD7, UART3.SHLD8
SHLD7: DIRECT_USB3.SHLD1, DIRECT_USB3.SHLD2, DIRECT_USB3.SHLD3, DIRECT_USB3.SHLD4, DIRECT_USB3.SHLD5, DIRECT_USB3.SHLD6, DIRECT_USB3.SHLD7, DIRECT_USB3.SHLD8, SHLD7.2
SHLD8: SHLD8.2, UART4.SHLD1, UART4.SHLD2, UART4.SHLD3, UART4.SHLD4, UART4.SHLD5, UART4.SHLD6, UART4.SHLD7, UART4.SHLD8
SHLD9: DIRECT_USB4.SHLD1, DIRECT_USB4.SHLD2, DIRECT_USB4.SHLD3, DIRECT_USB4.SHLD4, DIRECT_USB4.SHLD5, DIRECT_USB4.SHLD6, DIRECT_USB4.SHLD7, DIRECT_USB4.SHLD8, SHLD9.2
SHLD10: SHLD10.2, UART5.SHLD1, UART5.SHLD2, UART5.SHLD3, UART5.SHLD4, UART5.SHLD5, UART5.SHLD6, UART5.SHLD7, UART5.SHLD8
SHLD11: DIRECT_USB5.SHLD1, DIRECT_USB5.SHLD2, DIRECT_USB5.SHLD3, DIRECT_USB5.SHLD4, DIRECT_USB5.SHLD5, DIRECT_USB5.SHLD6, DIRECT_USB5.SHLD7, DIRECT_USB5.SHLD8, SHLD11.2
VIN: C8.1, D1.C, D5.C, D6.A, J9.1, Q2.1, R4.1, R20.2, U4.4
VIN1: C29.1, D11.A, D12.C, D13.C, J15.1, Q1.1, R25.2, R30.1, U11.4
VIN2: C44.1, D19.A, D20.C, D21.C, J23.1, Q3.1, R41.2, R46.1, U17.4
VIN3: C59.1, D27.A, D28.C, D29.C, J31.1, Q4.1, R57.2, R62.1, U23.4
VIN4: C74.1, D35.A, D36.C, D37.C, J39.1, Q5.1, R73.2, R78.1, U29.4
VIN5: C89.1, D43.A, D44.C, D45.C, J47.1, Q6.1, R89.2, R94.1, U35.4
V_BATT: C15.1, J8.2, J12.2, Q2.3, U4.3
V_BATT1: C30.1, J1.2, J3.2, Q1.3, U11.3
V_BATT2: C45.1, J17.2, J18.2, Q3.3, U17.3
V_BATT3: C60.1, J25.2, J26.2, Q4.3, U23.3
V_BATT4: C75.1, J33.2, J34.2, Q5.3, U29.3
V_BATT5: C90.1, J41.2, J42.2, Q6.3, U35.3
V_USB: C5.1, D5.A, U5.5, U7.15, UART.VBUS1, UART.VBUS2
V_USB1: C28.1, D13.A, U9.5, U10.15, UART1.VBUS1, UART1.VBUS2
V_USB2: C43.1, D21.A, U15.5, U16.15, UART2.VBUS1, UART2.VBUS2
V_USB3: C58.1, D29.A, U21.5, U22.15, UART3.VBUS1, UART3.VBUS2
V_USB4: C73.1, D37.A, U27.5, U28.15, UART4.VBUS1, UART4.VBUS2
V_USB5: C88.1, D45.A, U33.5, U34.15, UART5.VBUS1, UART5.VBUS2
V_USB_1: D12.A, DIRECT_USB1.VBUS1, DIRECT_USB1.VBUS2, U8.5
V_USB_2: D1.A, DIRECT_USB.VBUS1, DIRECT_USB.VBUS2, U3.5
V_USB_3: D20.A, DIRECT_USB2.VBUS1, DIRECT_USB2.VBUS2, U14.5
V_USB_4: D28.A, DIRECT_USB3.VBUS1, DIRECT_USB3.VBUS2, U20.5
V_USB_5: D36.A, DIRECT_USB4.VBUS1, DIRECT_USB4.VBUS2, U26.5
V_USB_6: D44.A, DIRECT_USB5.VBUS1, DIRECT_USB5.VBUS2, U32.5
XBEE_D+/SDA: J2.7, U6.3
XBEE_D+/SDA1: J14.7, U12.3
XBEE_D+/SDA2: J22.7, U18.3
XBEE_D+/SDA3: J30.7, U24.3
XBEE_D+/SDA4: J38.7, U30.3
XBEE_D+/SDA5: J46.7, U36.3
XBEE_D-: J2.8, U6.4
XBEE_D-1: J14.8, U12.4
XBEE_D-2: J22.8, U18.4
XBEE_D-3: J30.8, U24.4
XBEE_D-4: J38.8, U30.4
XBEE_D-5: J46.8, U36.4
